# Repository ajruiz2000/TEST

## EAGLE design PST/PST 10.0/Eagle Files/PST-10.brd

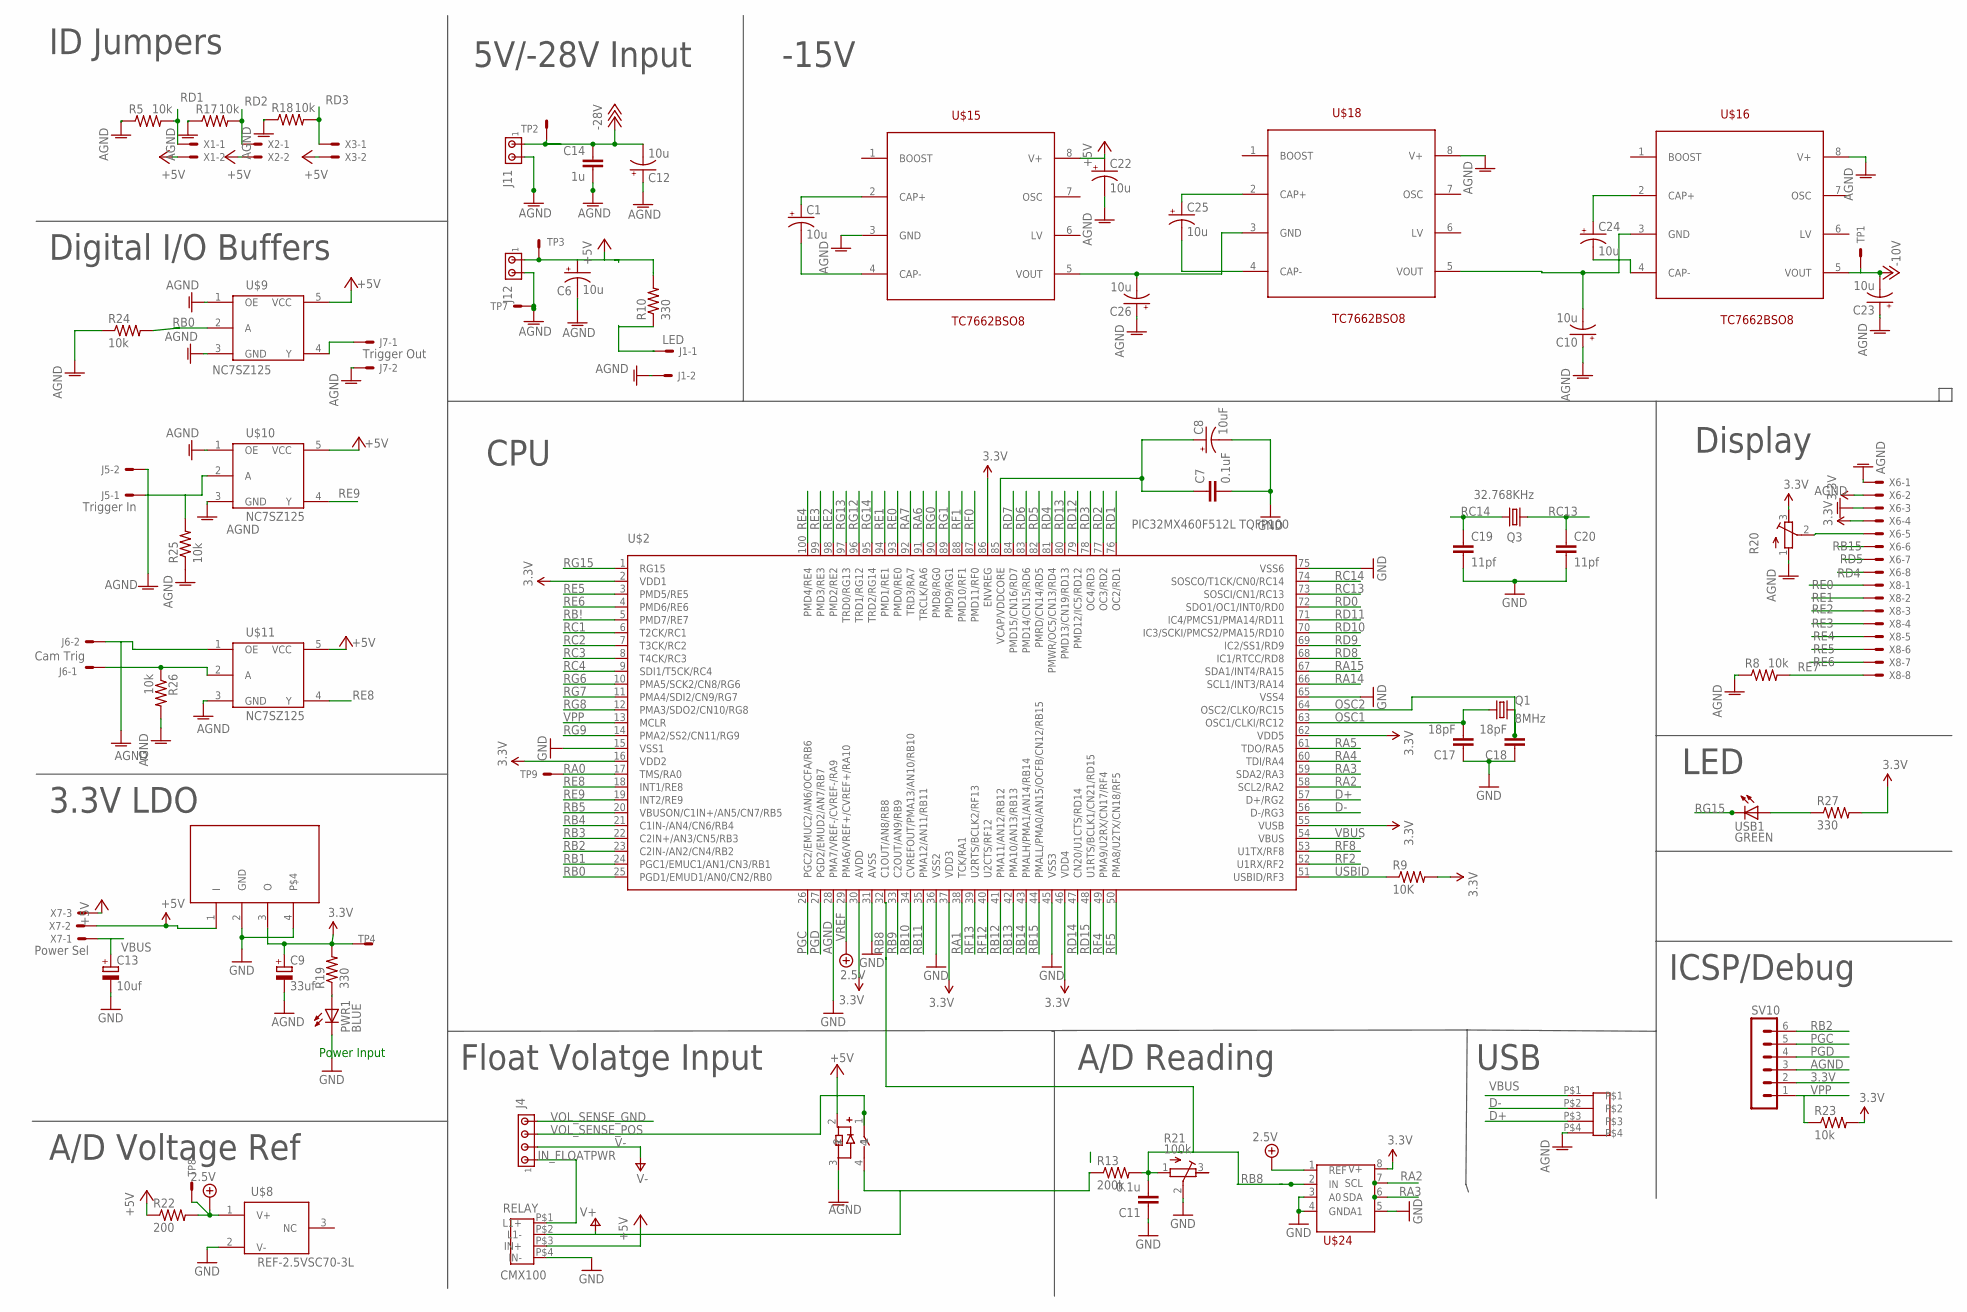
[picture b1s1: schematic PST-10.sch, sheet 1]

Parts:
C1, C6, C10, C12, C22, C23, C24, C25, C26: 10u; E2-4
C7: 0.1uF; 0402-CAP
C8: 10uF; EIA3528
C9: 33uf; E5-4
C11: 0.1u; C1206
C13: 10uf; E5-4
C14: 1u; C025-024X044
C17, C18: 18pF; 0402-CAP
C19, C20: 11pf; 0402-CAP
J1: LED; 6410-02
J4: MTA04-156; 1X4MTA
J5: Trigger In; 6410-02
J6: Cam Trig; 6410-02
J7: Trigger Out; 6410-02
J11, J12: MTA02-156; 1X2MTA
PWR1: BLUE; LED-0603
Q1: 8MHz; CRYSTAL-SMD-5X3
Q3: 32.768KHz; CRYSTAL-32KHZ-SMD
R5, R8, R17, R18, R23, R24, R25, R26: 10k; R1206
R9: 10K; 0402-RES
R10, R19, R27: 330; 0402-RES
R13: 200k; R1206
R20: R-TRIMM3296W; RTRIM3296W
R21: 100k; RTRIM3296W
R22: 200; R1206
RELAY: CMX100; CMX100D10
SV10: MA06-1
TP1, TP2, TP3, TP4, TP7, TP8, TP9: TESTPOINT
U$2: PIC32MX460F512L TQFP100; TQFP100
U$7: 3.3VREG; SOT223
U$8: REF-2.5VSC70-3L; SC70-3L
U$9, U$10, U$11: NC7SZ125; SC70-5
U$15, U$16, U$18: TC7662BSO8; SO8
U$22: 9007-05-01
U$24: ADS7823MOSOP-08; MSOP08
USB: USB-B1KSW6; USBB1K-4-VER
USB1: GREEN; LED-0603
X1, X2, X3: 22-23-2021
X6, X8: 22-23-2081
X7: Power Sel; 22-23-2031

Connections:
3.3V: C9.+, R9.2, R19.2, R20.3 (A), R23.2, R27.2, SV10.2, TP4.TP, U$2.2 (VDD1), U$2.16 (VDD2), U$2.30 (AVDD), U$2.37 (VDD3), U$2.46 (VDD4), U$2.55 (VUSB), U$2.62 (VDD5), U$2.86 (ENVREG), U$7.3 (O), U$24.8 (V+), X6.2, X6.4
5V: U$7.1 (I), X7.2
+5V: C6.+, C22.+, J12.1, R10.2, R22.1, RELAY.P$3 (IN+), TP3.TP, U$9.5 (VCC), U$10.5 (VCC), U$11.5 (VCC), U$15.8 (V+), U$22.2, X1.2, X2.2, X3.2, X7.3; also elsewhere on the board
-10V: C23.-, TP1.TP, U$16.5 (VOUT); also elsewhere on the board
-18V: C12.-, C14.1, J11.1, TP2.TP; also elsewhere on the board
AGND: C6.-, C7.2, C8.C (-), C9.-, C10.+, C11.1, C12.+, C13.-, C14.2, C17.1, C18.1, C19.2, C20.2, C22.-, C23.+, C26.+, J1.2, J5.2, J6.2, J7.2, J11.2, J12.2, PWR1.C, R5.1, R8.1, R17.1, R18.1, R20.1 (E), R21.2 (S), R24.1, R25.1, R26.2, RELAY.P$4 (IN-), SV10.3, TP7.TP, U$2.15 (VSS1), U$2.28 (PMA7/VREF-/CVREF-/RA9), U$2.31 (AVSS), U$2.36 (VSS2), U$2.45 (VSS3), U$2.65 (VSS4), U$2.75 (VSS6), U$7.2 (GND), U$7.4, U$8.2 (V-), U$9.1 (OE), U$9.3 (GND), U$10.1 (OE), U$10.3 (GND), U$11.1 (OE), U$11.3 (GND), U$15.3 (GND), U$16.8 (V+), U$18.8 (V+), U$22.3, U$24.3 (A0), U$24.4 (GND), U$24.5 (A1), USB.P$4, X6.1, X6.3; also elsewhere on the board
D+: U$2.57 (D+/RG2), USB.P$3
D-: U$2.56 (D-/RG3), USB.P$2
IN_FLOATPWR: J4.1, RELAY.P$1 (L1+)
unnamed: J6.1, R26.1, U$11.2 (A)
unnamed: R20.2 (S), X6.5
unnamed: C1.+, U$15.2 (CAP+)
unnamed: J1.1, R10.1
unnamed: PWR1.A, R19.1
unnamed: J7.1, U$9.4 (Y)
unnamed: C1.-, U$15.4 (CAP-)
unnamed: J5.1, R25.2, U$10.2 (A)
unnamed: C25.+, U$18.2 (CAP+)
unnamed: C10.-, U$16.3 (GND), U$18.5 (VOUT)
unnamed: C25.-, U$18.4 (CAP-)
unnamed: C24.+, U$16.2 (CAP+)
unnamed: R27.1, USB1.A
unnamed: C24.-, U$16.4 (CAP-)
unnamed: C26.-, U$15.5 (VOUT), U$18.3 (GND)
unnamed: C7.1, C8.A (+), U$2.85 (VCAP/VDDCORE)
OSC1: C17.2, Q1.1, U$2.63 (OSC1/CLKI/RC12)
OSC2: C18.2, Q1.3 (2), U$2.64 (OSC2/CLKO/RC15)
PGC: SV10.5, U$2.26 (PGC2/EMUC2/AN6/OCFA/RB6)
PGD: SV10.4, U$2.27 (PGD2/EMUD2/AN7/RB7)
RA0: TP9.TP, U$2.17 (TMS/RA0)
RA1: U$2.38 (TCK/RA1)
RA2: U$2.58 (SCL2/RA2), U$24.7 (SCL)
RA3: U$2.59 (SDA2/RA3), U$24.6 (SDA)
RA4: U$2.60 (TDI/RA4)
RA5: U$2.61 (TDO/RA5)
RA6: U$2.91 (TRCLK/RA6)
RA7: U$2.92 (TRD3/RA7)
RA14: U$2.66 (SCL1/INT3/RA14)
RA15: U$2.67 (SDA1/INT4/RA15)
RB0: R24.2, U$2.25 (PGD1/EMUD1/AN0/CN2/RB0), U$9.2 (A)
RB1: U$2.24 (PGC1/EMUC1/AN1/CN3/RB1)
RB2: SV10.6, U$2.23 (C2IN-/AN2/CN4/RB2)
RB3: U$2.22 (C2IN+/AN3/CN5/RB3)
RB4: U$2.21 (C1IN-/AN4/CN6/RB4)
RB5: U$2.20 (VBUSON/C1IN+/AN5/CN7/RB5)
RB8: C11.2, R13.2, R21.1 (E), U$2.32 (C1OUT/AN8/RB8), U$24.2 (IN)
RB9: U$2.33 (C2OUT/AN9/RB9)
RB10: U$2.34 (CVREFOUT/PMA13/AN10/RB10)
RB11: U$2.35 (PMA12/AN11/RB11)
RB12: U$2.41 (PMA11/AN12/RB12)
RB13: U$2.42 (PMA10/AN13/RB13)
RB14: U$2.43 (PMALH/PMA1/AN14/RB14)
RB15: U$2.44 (PMALL/PMA0/AN15/OCFB/CN12/RB15), X6.6
RB!: U$2.5 (PMD7/RE7)
RC1: U$2.6 (T2CK/RC1); also elsewhere on the board
RC2: U$2.7 (T3CK/RC2)
RC3: U$2.8 (T4CK/RC3)
RC4: U$2.9 (SDI1/T5CK/RC4)
RC13: C20.1, Q3.X1 (1), U$2.73 (SOSCI/CN1/RC13)
RC14: C19.1, Q3.X2 (2), U$2.74 (SOSCO/T1CK/CN0/RC14)
RD0: U$2.72 (SDO1/OC1/INT0/RD0)
RD1: R5.2, U$2.76 (OC2/RD1), X1.1
RD2: R17.2, U$2.77 (OC3/RD2), X2.1
RD3: R18.2, U$2.78 (OC4/RD3), X3.1
RD4: U$2.81 (PMWR/OC5/CN13/RD4), X6.8
RD5: U$2.82 (PMRD/CN14/RD5), X6.7
RD6: U$2.83 (PMD14/CN15/RD6)
RD7: U$2.84 (PMD15/CN16/RD7)
RD8: U$2.68 (IC1/RTCC/RD8)
RD9: U$2.69 (IC2/SS1/RD9)
RD10: U$2.70 (IC3/SCKI/PMCS2/PMA15/RD10)
RD11: U$2.71 (IC4/PMCS1/PMA14/RD11)
RD12: U$2.79 (PMD12/IC5/RD12)
RD13: U$2.80 (PMD13/CN19/RD13)
RD14: U$2.47 (CN20/U1CTS/RD14)
RD15: U$2.48 (U1RTS/BCLK1/CN21/RD15)
RE0: U$2.93 (PMD0/RE0), X8.1
RE1: U$2.94 (PMD1/RE1), X8.2
RE2: U$2.98 (PMD2/RE2), X8.3
RE3: U$2.99 (PMD3/RE3), X8.4
RE4: U$2.100 (PMD4/RE4), X8.5
RE5: U$2.3 (PMD5/RE5), X8.6
RE6: U$2.4 (PMD6/RE6), X8.7
RE7: R8.2, X8.8
RE8: U$2.18 (INT1/RE8), U$11.4 (Y)
RE9: U$2.19 (INT2/RE9), U$10.4 (Y)
RF0: U$2.87 (PMD11/RF0)
RF1: U$2.88 (PMD10/RF1)
RF2: U$2.52 (U1RX/RF2)
RF4: U$2.49 (PMA9/U2RX/CN17/RF4)
RF5: U$2.50 (PMA8/U2TX/CN18/RF5)
RF8: U$2.53 (U1TX/RF8)
RF12: U$2.40 (U2CTS/RF12)
RF13: U$2.39 (U2RTS/BCLK2/RF13)
RG0: U$2.90 (PMD8/RG0)
RG1: U$2.89 (PMD9/RG1)
RG6: U$2.10 (PMA5/SCK2/CN8/RG6)
RG7: U$2.11 (PMA4/SDI2/CN9/RG7)
RG8: U$2.12 (PMA3/SDO2/CN10/RG8)
RG9: U$2.14 (PMA2/SS2/CN11/RG9)
RG12: U$2.96 (TRD1/RG12)
RG13: U$2.97 (TRD0/RG13)
RG14: U$2.95 (TRD2/RG14)
RG15: U$2.1 (RG15), USB1.C
USBID: R9.1, U$2.51 (USBID/RF3)
V+: R13.1, RELAY.P$2 (L1-), U$22.4; also elsewhere on the board
V-: J4.2; also elsewhere on the board
VBUS: C13.+, U$2.54 (VBUS), USB.P$1, X7.1
VOL_SENSE_GND: J4.4; also elsewhere on the board
VOL_SENSE_POS: J4.3, U$22.1
VPP: R23.1, SV10.1, U$2.13 (MCLR)
VREF: R22.2, TP8.TP, U$2.29 (PMA6/VREF+/CVREF+/RA10), U$8.1 (V+), U$24.1 (REF)

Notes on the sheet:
Power Input
ID Jumpers
Digital I/O Buffers
3.3V LDO
CPU
Display
LED
ICSP/Debug
USB
A/D Voltage Ref
A/D Reading
5V/-28V Input
Float Volatge Input
-15V

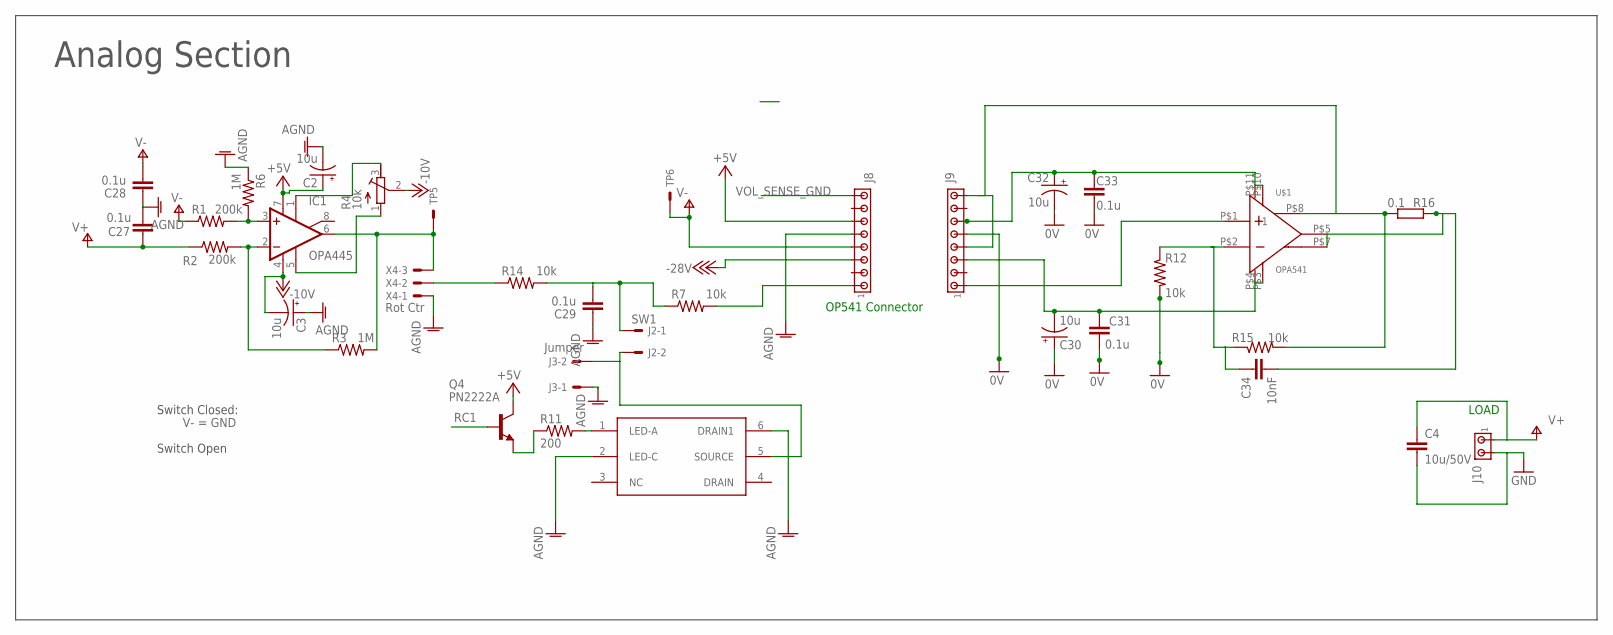
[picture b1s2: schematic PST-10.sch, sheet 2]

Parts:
C2, C3, C30, C32: 10u; E2-4
C4: 10u/50V; C1206
C27, C28, C29: 0.1u; C1206
C31, C33: 0.1u; C025-024X044
C34: 10nF; C1206
IC1: OPA445; DIL08
J2: SW1; 6410-02
J3: Jumper; 6410-02
J8, J9: MTA08-156; 1X8MTA
J10: MTA02-156; 1X2MTA
Q4: PN2222A; TO92-
R1, R2: 200k; R1206
R3, R6: 1M; R1206
R4: 10k; RTRIM3296W
R7, R12, R14, R15: 10k; R1206
R11: 200; R1206
R16: 0.1; V235/17
TP5, TP6: TESTPOINT
U$1: OPA541
U$4: PS7113DIL06; DIL06
X4: Rot Ctr; 22-23-2031

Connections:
0V: C30.+, C31.2, C32.-, C33.1, J9.5, R12.2
+5V: C2.+, IC1.7 (V+), J8.6, Q4.3 (C); also elsewhere on the board
-10V: C3.-, IC1.4 (V-), R4.2 (S); also elsewhere on the board
-18V: J8.3; also elsewhere on the board
AGND: C2.-, C3.+, C4.2, C27.2, C28.1, C29.1, J3.1, J8.5, J10.2, R6.1, U$4.2 (LED-C), U$4.6 (DRAIN1), X4.1; also elsewhere on the board
unnamed: IC1.3 (+IN), R1.2, R6.2
unnamed: IC1.1 (ON1), R4.3 (A)
unnamed: J8.1, R7.2
unnamed: J9.4, J9.8, R15.2, R16.1, U$1.P$8 (CURRENT_SENSE)
unnamed: IC1.6 (OUT), R3.2, TP5.TP, X4.3
unnamed: IC1.2 (-IN), R2.2, R3.1
unnamed: R14.1, X4.2
unnamed: J2.2, J3.2, U$4.5 (SOURCE)
unnamed: R11.2, U$4.1 (LED-A)
unnamed: Q4.1 (E), R11.1
unnamed: C29.2, J2.1, R7.1, R14.2
unnamed: C30.-, C31.1, J9.3, U$1.P$3 (-VS), U$1.P$4 (-VS2)
unnamed: IC1.5 (OPT), R4.1 (E)
unnamed: C32.+, C33.2, J9.6, U$1.P$10 (V+), U$1.P$11 (+VS2)
unnamed: J9.1, U$1.P$1 (1)
unnamed: C34.2, R16.2, U$1.P$5 (VOUT), U$1.P$7 (VOUT_2)
unnamed: C34.1, R12.1, R15.1, U$1.P$2 (IN-)
RC1: Q4.2 (B); also elsewhere on the board
V+: C4.1, C27.1, J10.1, R2.1; also elsewhere on the board
V-: C28.2, J8.4, R1.1, TP6.TP; also elsewhere on the board
VOL_SENSE_GND: J8.8; also elsewhere on the board

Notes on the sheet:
Analog Section
Switch Closed:
Switch Open
OP541 Connector
V- = GND
LOAD

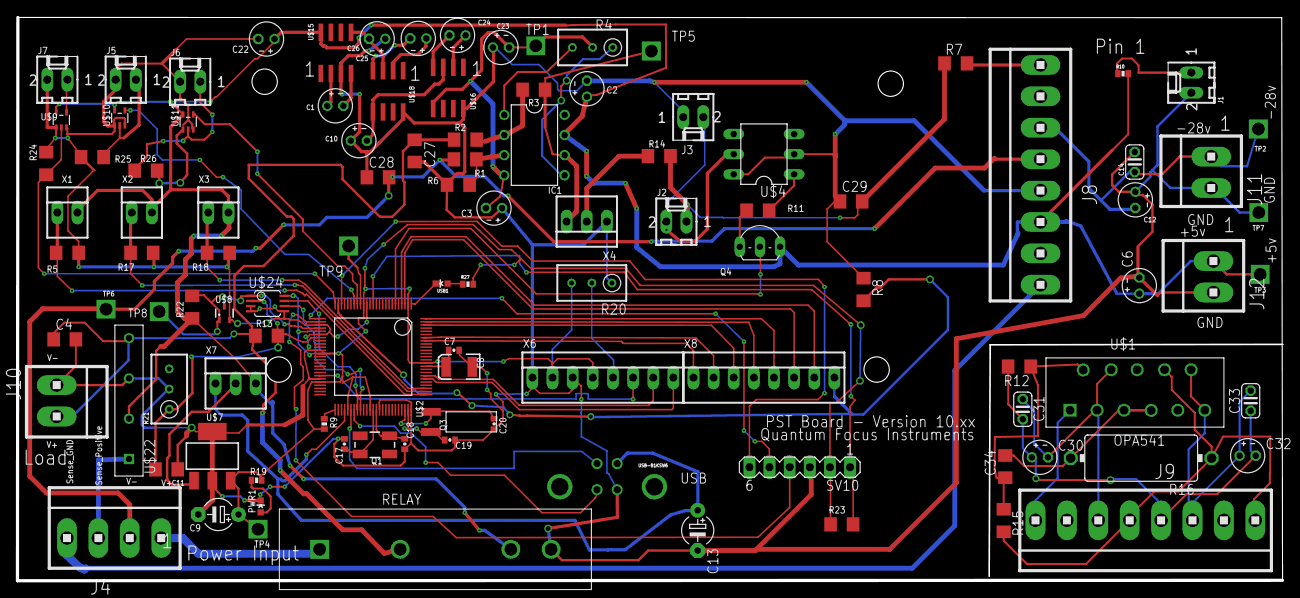
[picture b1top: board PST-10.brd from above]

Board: 2 copper layers, 159.6 x 71.1 mm, 107 parts (0 on the bottom side), 81 nets.
